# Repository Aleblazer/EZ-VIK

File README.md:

# EZ-VIK
 Easy to solder surface mount VIK connector.

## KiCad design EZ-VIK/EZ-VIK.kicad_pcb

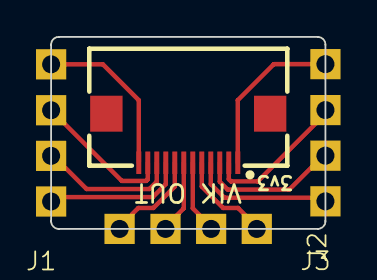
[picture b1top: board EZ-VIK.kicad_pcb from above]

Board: 2 copper layers, 15.2 x 10.7 mm, 4 parts (0 on the bottom side), 12 nets.

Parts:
J1, J2, J3: Conn_01x04; Castellated2.54.01x04
J4: vik-keyboard-connector-horizontal

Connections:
+3V3: J3.1, J4.1 (3V3)
+5V: J2.3, J4.6 (5V)
GND: J3.2, J4.2 (GND)
GP_AD1: J2.2, J4.7 (GP_AD1)
GP_AD2: J1.4, J4.9 (GP_AD2)
MISO: J1.2, J4.11 (MISO)
MOSI: J2.1, J4.8 (MOSI)
RGB_DO: J2.4, J4.5 (RGB_DO)
SCL: J3.4, J4.4 (SCL)
SCLK: J1.1, J4.12 (SCLK)
SDA: J3.3, J4.3 (SDA)
SPI_CS: J1.3, J4.10 (SPI_CS)

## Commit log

2024-05-06 Initial update
2024-05-06 Added PCB footprint for the EZ-VIK
2024-05-08 Split into full size and mini
    Added Mini branch, and changed main branch to the full size VIK connector.
2024-05-08 Added footprints
    Added pad footprints for Mini and Full size VIK connectors, and with/without included optional connector footprints for PCBA.
2024-05-08 Finished tracework.
